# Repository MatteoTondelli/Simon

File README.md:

# Simon
Arduino version of Milton Bradleys' Simon Game.

# License

Simon  © 2026 by Matteo Tondelli is licensed under Creative Commons Attribution-NonCommercial-ShareAlike 4.0 International. To view a copy of this license, visit https://creativecommons.org/licenses/by-nc-sa/4.0/

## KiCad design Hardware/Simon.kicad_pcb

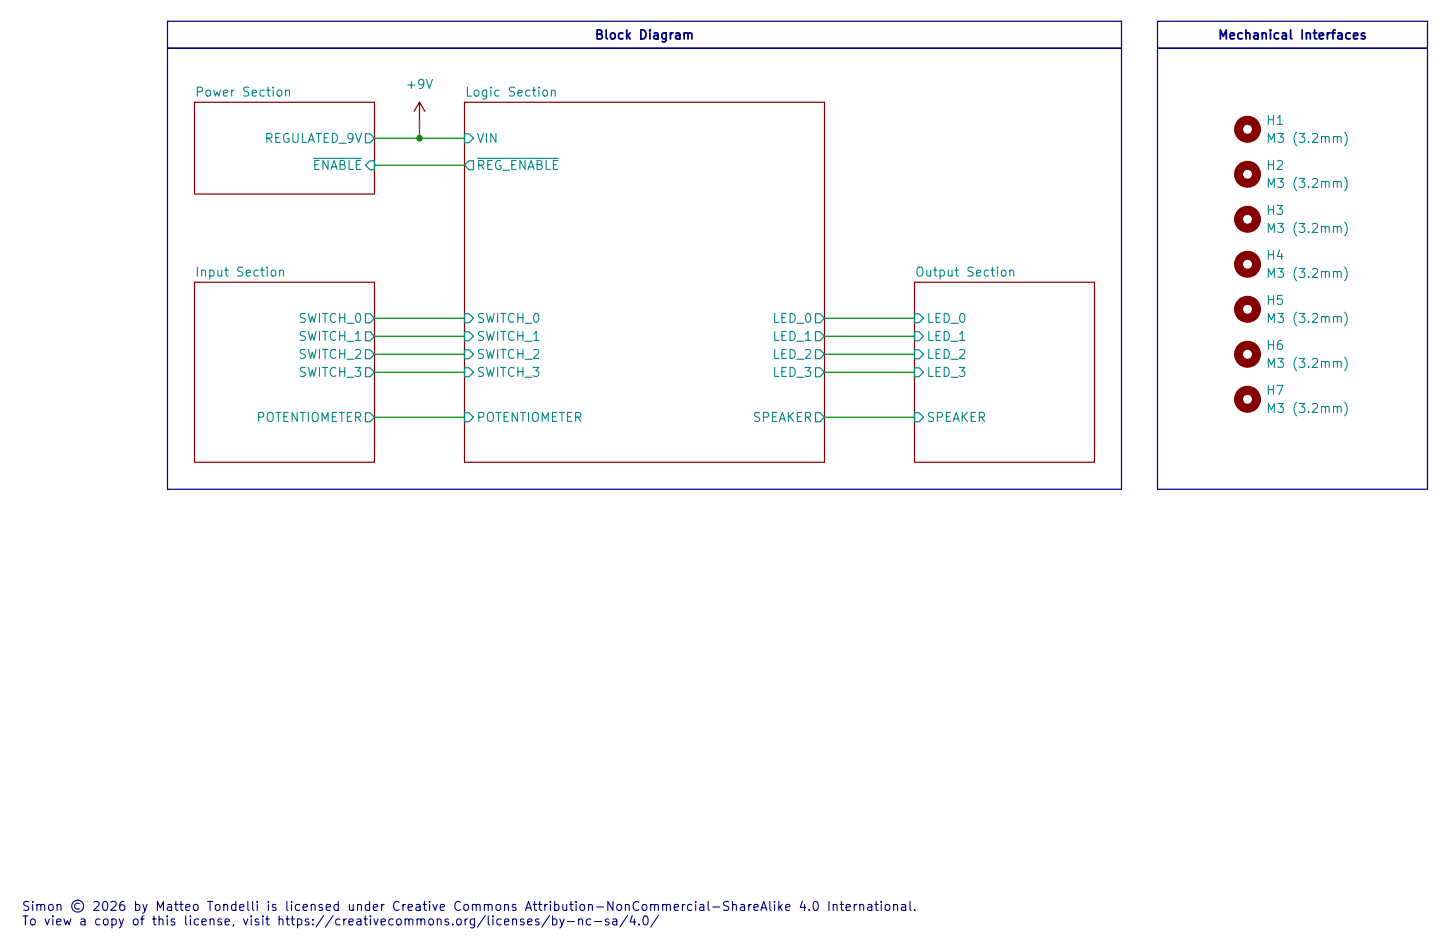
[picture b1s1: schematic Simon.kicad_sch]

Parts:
H1, H2, H3, H4, H5, H6, H7: M3 (3.2mm); MountingHole_3.2mm_M3

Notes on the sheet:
Simon © 2026 by Matteo Tondelli is licensed under Creative Commons Attribution-NonCommercial-ShareAlike 4.0 International. To view a copy of this license, visit https://creativecommons.org/licenses/by-nc-sa/4.0/
Block Diagram
Mechanical Interfaces

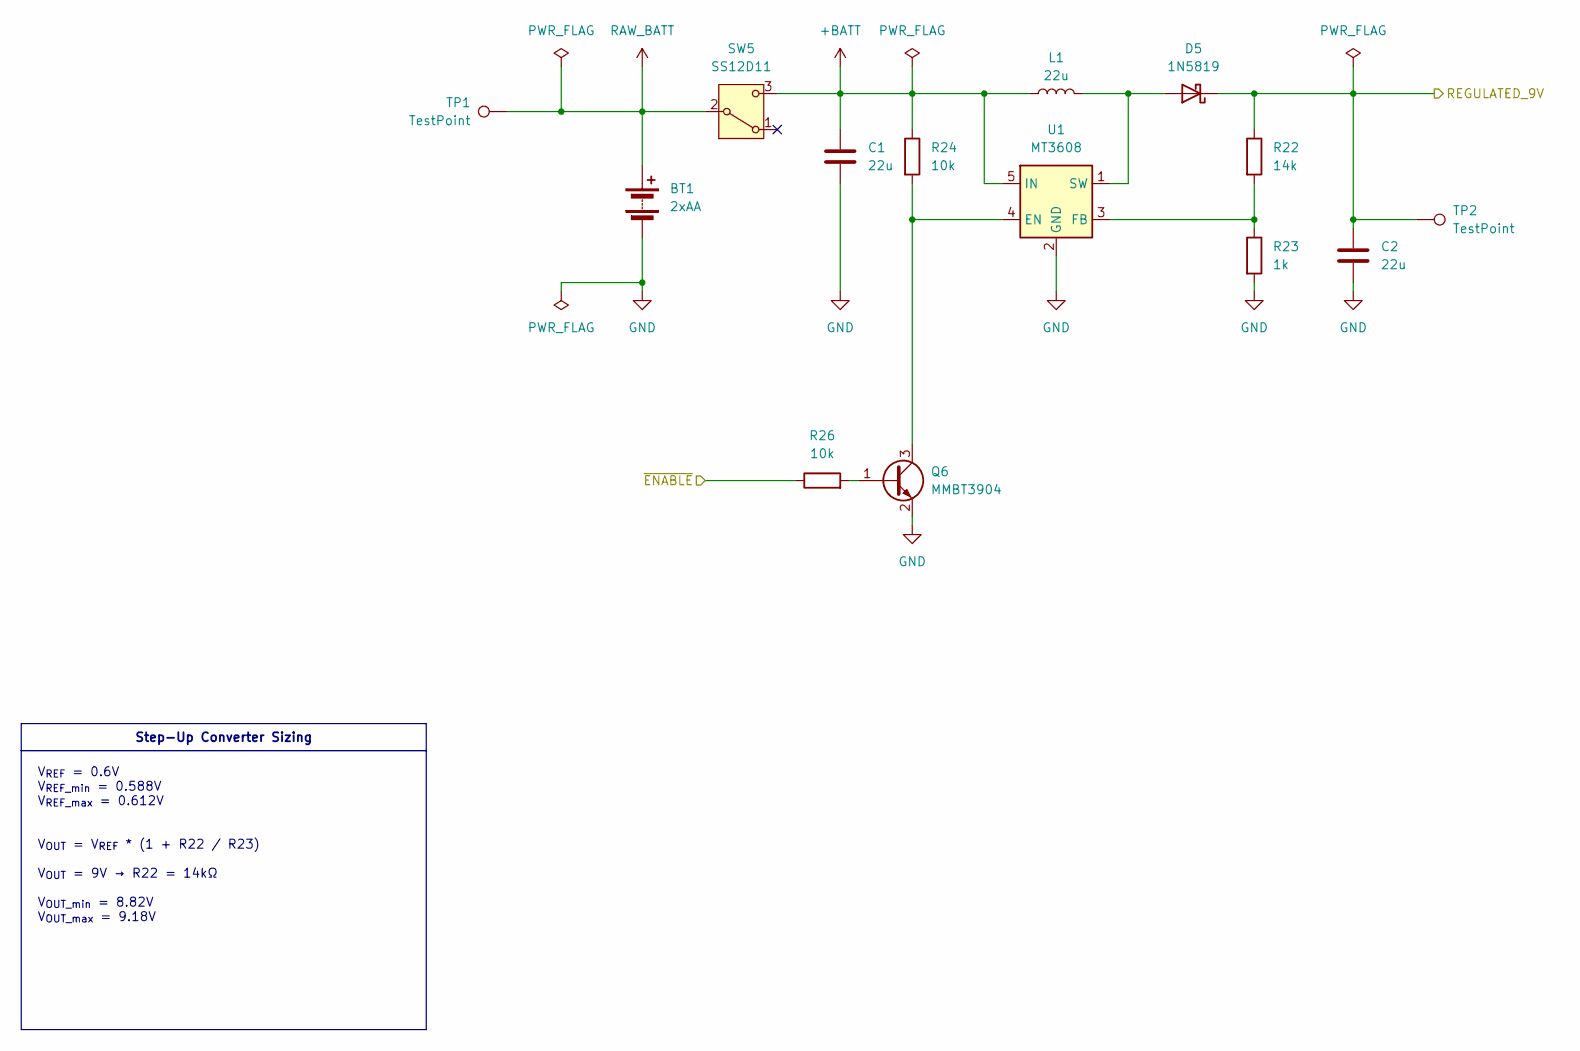
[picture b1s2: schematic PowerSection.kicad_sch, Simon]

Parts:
BT1: 2xAA; BatteryHolder_Keystone_2462_2xAA
C1, C2: 22u; C_0805_2012Metric
D5: 1N5819; D_SMA
L1: 22u; CDRH104R; MPN CDRH104RNP-220N
Q6: MMBT3904; SOT-23
R22: 14k; R_0805_2012Metric
R23: 1k; R_0805_2012Metric
R24, R26: 10k; R_0805_2012Metric
SW5: SS12D11; SS12D11G5
TP1, TP2: TestPoint; TestPoint_Pad_D1.0mm
U1: MT3608; SOT-23-6

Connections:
+9V: C2.1, D5.1 (K), R22.1, TP2.1 (1_1); also elsewhere on the board
+BATT: C1.1, L1.1, R24.1, SW5.3 (C), U1.5 (IN)
/Logic Section/~REG_ENABLE: R26.1; also elsewhere on the board
GND: BT1.2 (-), C1.2, C2.2, Q6.2 (E), R23.2, U1.2 (GND); also elsewhere on the board
unnamed: D5.2 (A), L1.2, U1.1 (SW)
unnamed: Q6.1 (B), R26.2
unnamed: Q6.3 (C), R24.2, U1.4 (EN)
unnamed: R22.2, R23.1, U1.3 (FB)
RAW_BATT: BT1.1 (+), SW5.2 (B), TP1.1 (1_1)

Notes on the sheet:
Step-Up Converter Sizing
V_{REF} = 0.6V V_{REF_min} = 0.588V V_{REF_max} = 0.612V V_{OUT} = V_{REF} * (1 + R22 / R23) V_{OUT} = 9V → R22 = 14kΩ V_{OUT_min} = 8.82V V_{OUT_max} = 9.18V

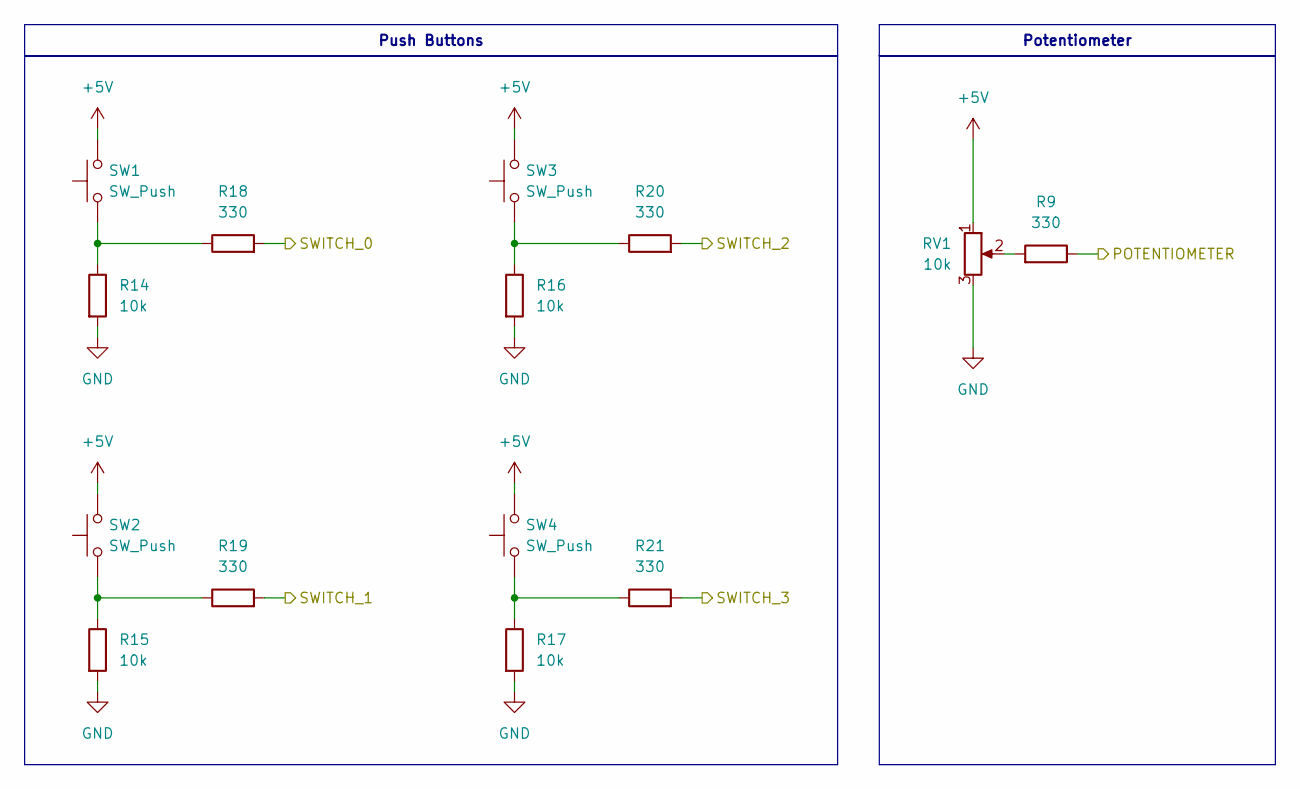
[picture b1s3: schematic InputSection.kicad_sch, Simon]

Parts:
R9, R18, R19, R20, R21: 330; R_0805_2012Metric
R14, R15, R16, R17: 10k; R_0805_2012Metric
RV1: 10k; Potentiometer_Runtron_RM-065_Vertical; MPN RM065-103
SW1, SW2, SW3, SW4: SW_Push; SW_MX

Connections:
+5V: RV1.1, SW1.2, SW2.2, SW3.2, SW4.2; also elsewhere on the board
/Input Section/POTENTIOMETER: R9.1; also elsewhere on the board
/Input Section/SWITCH_0: R18.2; also elsewhere on the board
/Input Section/SWITCH_1: R19.2; also elsewhere on the board
/Input Section/SWITCH_2: R20.2; also elsewhere on the board
/Input Section/SWITCH_3: R21.2; also elsewhere on the board
GND: R14.2, R15.2, R16.2, R17.2, RV1.3; also elsewhere on the board
unnamed: R9.2, RV1.2
unnamed: R14.1, R18.1, SW1.1
unnamed: R15.1, R19.1, SW2.1
unnamed: R16.1, R20.1, SW3.1
unnamed: R17.1, R21.1, SW4.1

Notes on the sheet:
Push Buttons
Potentiometer

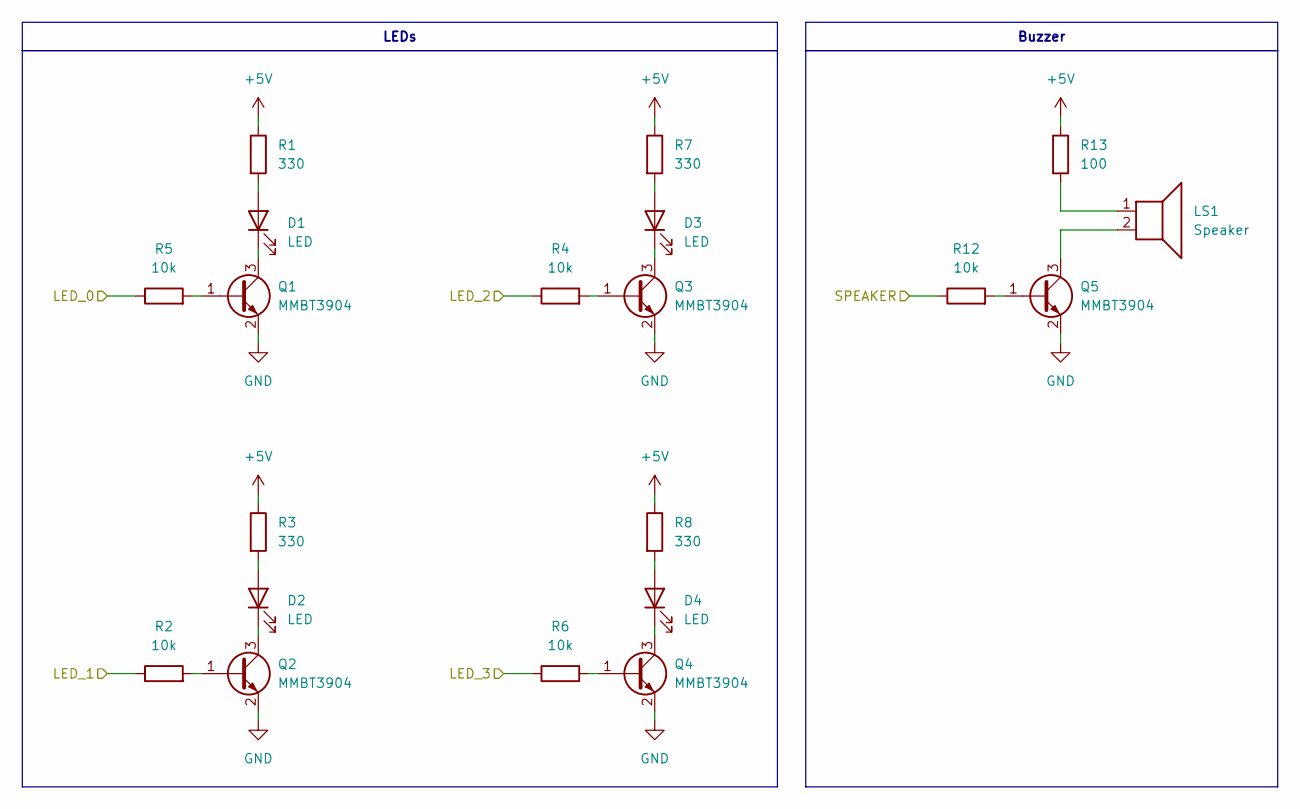
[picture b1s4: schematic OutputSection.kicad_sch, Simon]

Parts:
D1, D2, D3, D4: LED; LED_D10.0mm
LS1: Speaker; Buzzer
Q1, Q2, Q3, Q4, Q5: MMBT3904; SOT-23
R1, R3, R7, R8: 330; R_0805_2012Metric
R2, R4, R5, R6, R12: 10k; R_0805_2012Metric
R13: 100; R_0805_2012Metric

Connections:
+5V: R1.1, R3.1, R7.1, R8.1, R13.1; also elsewhere on the board
/Logic Section/LED_0: R5.1; also elsewhere on the board
/Logic Section/LED_1: R2.1; also elsewhere on the board
/Logic Section/LED_2: R4.1; also elsewhere on the board
/Logic Section/LED_3: R6.1; also elsewhere on the board
/Logic Section/SPEAKER: R12.1; also elsewhere on the board
GND: Q1.2 (E), Q2.2 (E), Q3.2 (E), Q4.2 (E), Q5.2 (E); also elsewhere on the board
unnamed: D1.2 (A), R1.2
unnamed: D1.1 (K), Q1.3 (C)
unnamed: D2.2 (A), R3.2
unnamed: D2.1 (K), Q2.3 (C)
unnamed: D3.2 (A), R7.2
unnamed: D3.1 (K), Q3.3 (C)
unnamed: D4.2 (A), R8.2
unnamed: D4.1 (K), Q4.3 (C)
unnamed: LS1.1, R13.2
unnamed: Q1.1 (B), R5.2
unnamed: Q2.1 (B), R2.2
unnamed: Q3.1 (B), R4.2
unnamed: Q4.1 (B), R6.2
unnamed: Q5.1 (B), R12.2
unnamed: LS1.2, Q5.3 (C)

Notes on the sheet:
LEDs
Buzzer

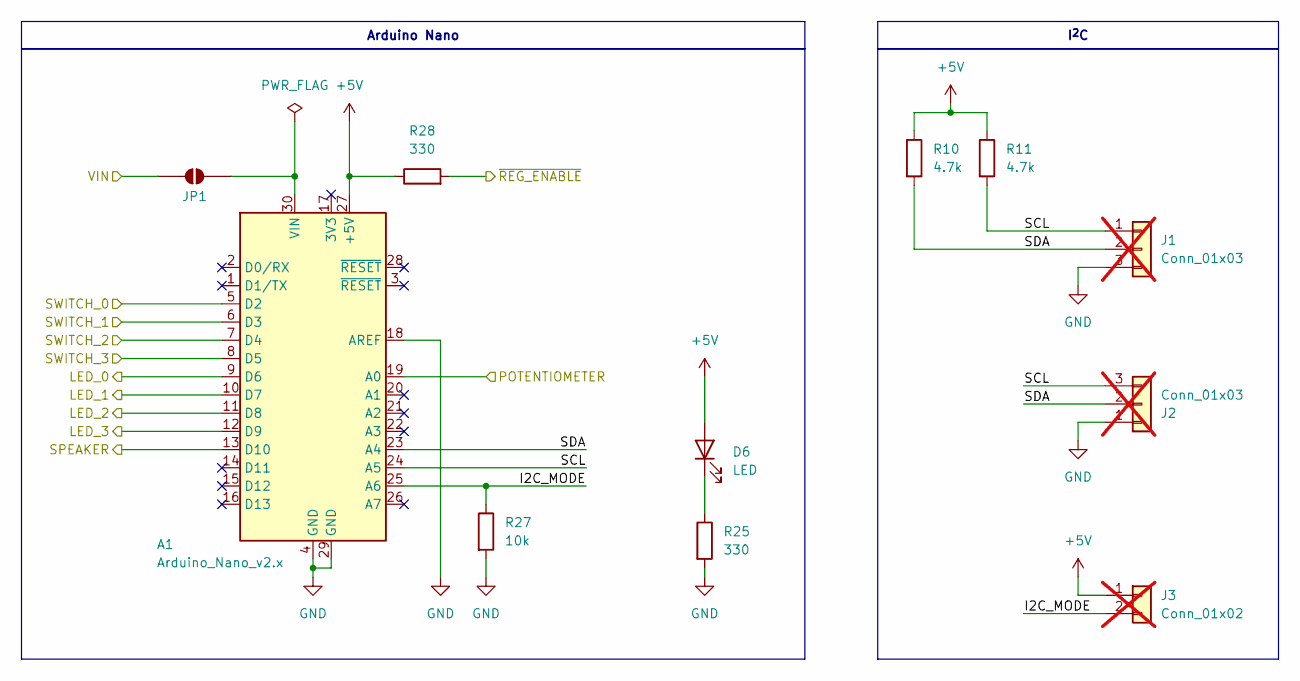
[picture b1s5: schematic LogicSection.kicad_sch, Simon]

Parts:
A1: Arduino_Nano_v2.x; Arduino_Nano
D6: LED; LED_D3.0mm_Horizontal_O6.35mm_Z2.0mm
J1, J2: Conn_01x03; PinSocket_1x03_P2.54mm_Horizontal; not fitted
J3: Conn_01x02; PinHeader_1x02_P2.54mm_Vertical; not fitted
JP1: SolderJumper_2_Open; SolderJumper-2_P1.3mm_Open_RoundedPad1.0x1.5mm
R10, R11: 4.7k; R_0805_2012Metric
R25, R28: 330; R_0805_2012Metric
R27: 10k; R_0805_2012Metric

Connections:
+5V: A1.27 (+5V), D6.2 (A), J3.1, R10.1, R11.1, R28.1; also elsewhere on the board
+9V: JP1.1 (A); also elsewhere on the board
/Input Section/POTENTIOMETER: A1.19 (A0); also elsewhere on the board
/Input Section/SWITCH_0: A1.5 (D2); also elsewhere on the board
/Input Section/SWITCH_1: A1.6 (D3); also elsewhere on the board
/Input Section/SWITCH_2: A1.7 (D4); also elsewhere on the board
/Input Section/SWITCH_3: A1.8 (D5); also elsewhere on the board
/Logic Section/I2C_MODE: A1.25 (A6), J3.2, R27.1
/Logic Section/LED_0: A1.9 (D6); also elsewhere on the board
/Logic Section/LED_1: A1.10 (D7); also elsewhere on the board
/Logic Section/LED_2: A1.11 (D8); also elsewhere on the board
/Logic Section/LED_3: A1.12 (D9); also elsewhere on the board
/Logic Section/SCL: A1.24 (A5), J1.1, J2.3, R11.2
/Logic Section/SDA: A1.23 (A4), J1.2, J2.2, R10.2
/Logic Section/SPEAKER: A1.13 (D10); also elsewhere on the board
/Logic Section/~REG_ENABLE: R28.2; also elsewhere on the board
GND: A1.4 (GND), A1.18 (AREF), A1.29 (GND), J1.3, J2.1, R25.2, R27.2; also elsewhere on the board
unnamed: A1.30 (VIN), JP1.2 (B)
unnamed: D6.1 (K), R25.1

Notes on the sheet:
I^{2}C
Arduino Nano

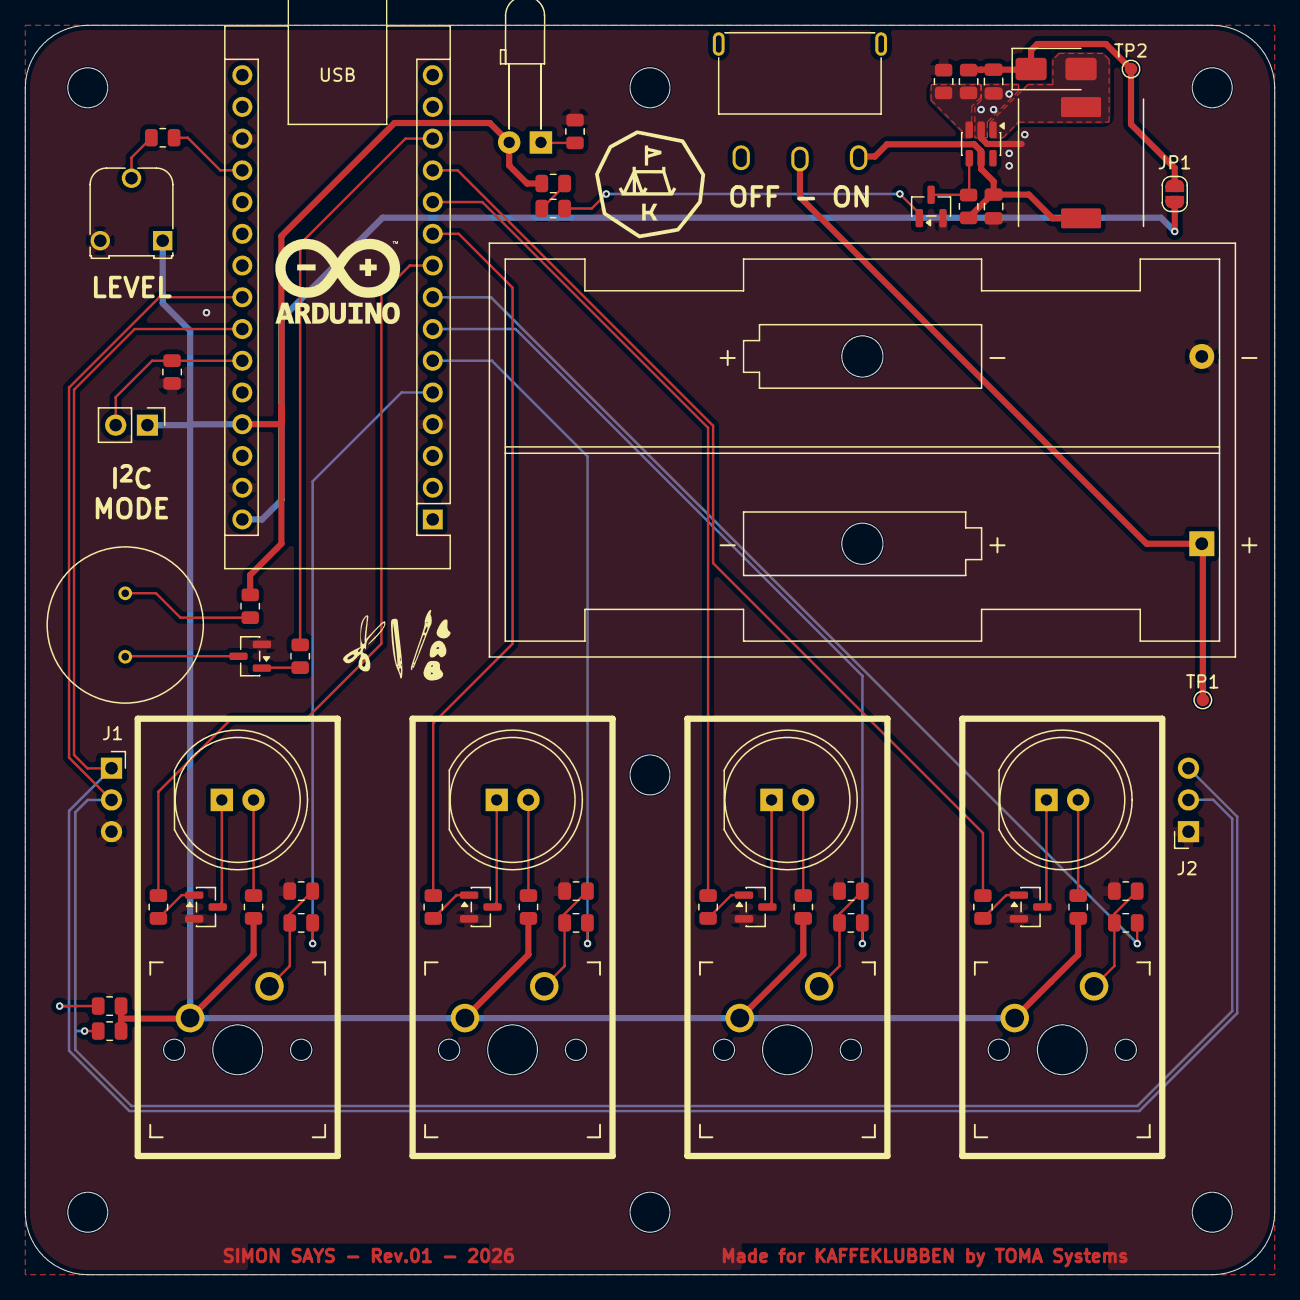
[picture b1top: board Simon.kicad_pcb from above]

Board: 2 copper layers, 100.0 x 100.0 mm, 66 parts (0 on the bottom side), 45 nets.

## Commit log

2026-03-28 Delete LICENSE
    Changing licensing.
2026-03-28 Added new license.
2026-03-28 Update README.md
    Added "License" section.
2026-03-28 Added KiCAD project.
2026-03-28 Updated files to KiCAD 10.
2026-03-31 Added KiCAD local library.
2026-03-31 Updated KiCAD project.
    - Added grouping in schematics.
    - Removed unnecessary net names in "LogicSection.kicad_sch".
    - Added 330R between +5V and nREG_ENABLE.
    - Changed path for 3D models.
2026-03-31 Added schematics PDF.
2026-03-31 Gerber files sent to production.
